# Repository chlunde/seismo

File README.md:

seismo
======

Based on [Build a Pendulum Seismometer for under $15](http://www.instructables.com/id/Build-a-Pendulum-Seismometer-for-under-15/) by [bikeframe](http://www.instructables.com/member/bikeframe/).

BOM
---

* [20Pcs 27mm Thickness 0.33mm Piezo Disc for Buzzer Pressure Sensor Speaker DIY](http://www.ebay.com/itm/151106903429) - 6 USD
* 4pcs 30g fishing sinker - 49 NOK
* [Raspberry Pi](http://www.raspberrypi.org/)
* [MCP3008 10 bit ADC](http://www.microchip.com/wwwproducts/Devices.aspx?dDocName=en010530)

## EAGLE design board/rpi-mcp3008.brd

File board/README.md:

Eagle schematics

jt-raspberry-pi.lbr from RAPIXT.com

RPI breakout board from https://github.com/bitraf/dlock13

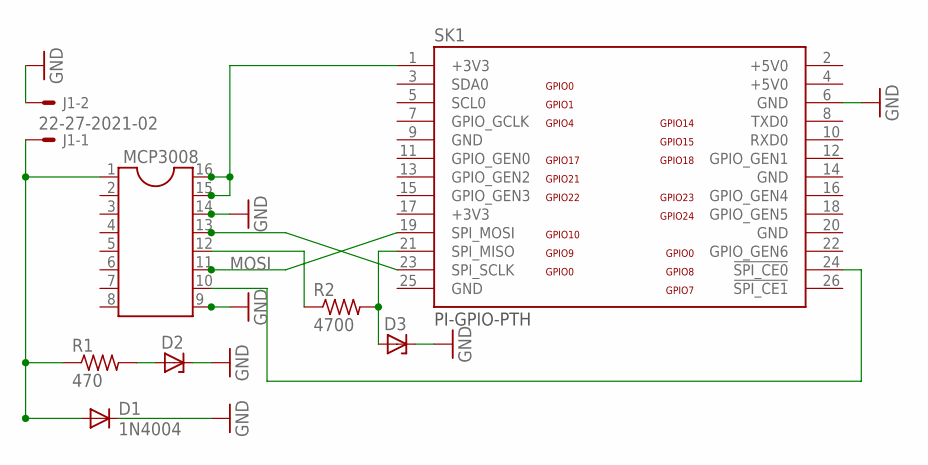
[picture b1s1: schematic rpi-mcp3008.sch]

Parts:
D1: 1N4004; DO41-10
D2, D3: ZENER-DIODEP1-Z12; P1Z12
J1: 22-27-2021-02; 6410-02
MCP3008: DIL16
R1: 470; 0207/7
R2: 4700; 0207/7
SK1: PI-GPIO-PTH; GPIO-CONNECTOR

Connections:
+3V3: SK1.17 (+3V3)
+5V0: SK1.2 (+5V0), SK1.4 (+5V0)
GND: D1.C, D2.C, D3.C, J1.2, MCP3008.9, MCP3008.14, SK1.6 (GND), SK1.9 (GND), SK1.14 (GND), SK1.20 (GND), SK1.25 (GND)
MOSI: MCP3008.11, SK1.19 (SPI_MOSI)
unnamed: D1.A, J1.1, MCP3008.1, R1.1
unnamed: MCP3008.15, MCP3008.16, SK1.1 (+3V3)
unnamed: MCP3008.10, SK1.24 (!SPI_CE0)
unnamed: D2.A, R1.2
unnamed: MCP3008.12, R2.1
unnamed: D3.A, R2.2, SK1.21 (SPI_MISO)
SCLK: MCP3008.13, SK1.23 (SPI_SCLK)

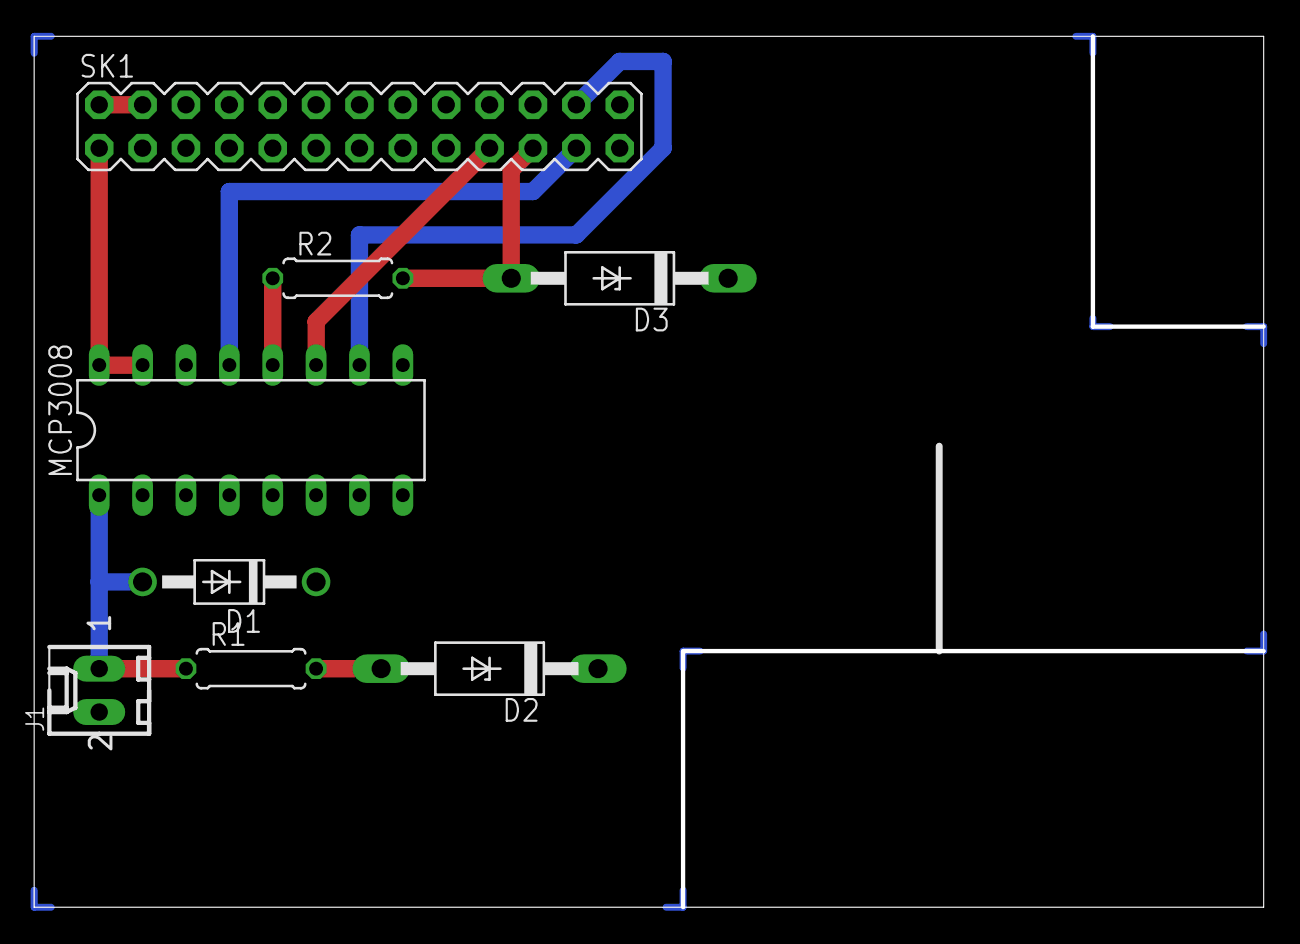
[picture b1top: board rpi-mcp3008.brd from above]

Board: 4 copper layers, 71.9 x 51.0 mm, 8 parts (0 on the bottom side), 10 nets.

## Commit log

2013-09-18 Add 3D models
2013-09-18 Add BOM
2013-09-18 Increase piezo thickness, reduce file size
2013-09-19 Larger, wider
2013-09-26 Add ADC type to BOM
2013-10-02 Initial board
2013-10-02 rapixt.com component included in .sch/.brd file
